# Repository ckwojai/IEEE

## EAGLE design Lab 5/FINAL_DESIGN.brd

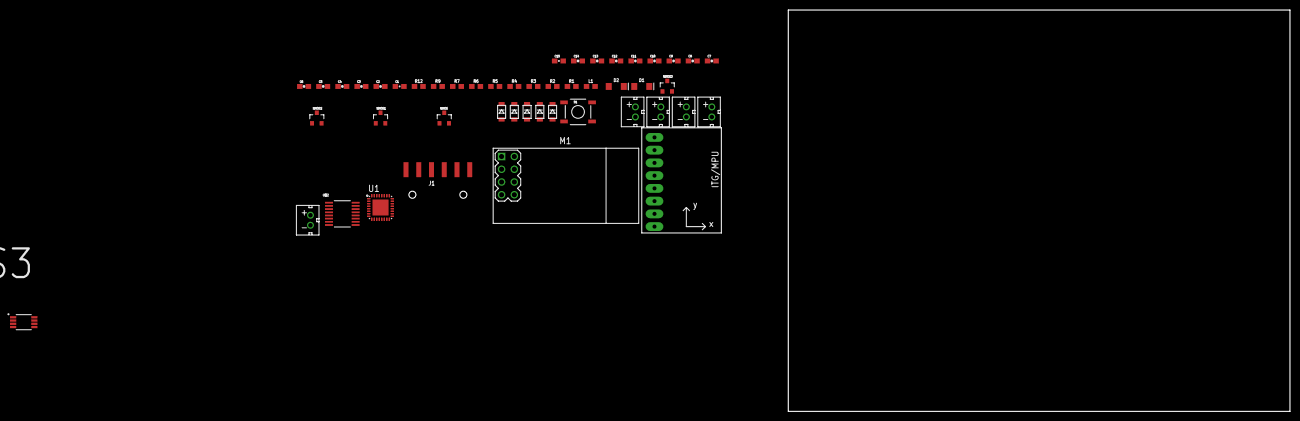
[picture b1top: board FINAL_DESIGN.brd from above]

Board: 2 copper layers, 100.0 x 80.0 mm, 48 parts (0 on the bottom side), 33 nets, no tracks yet.

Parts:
C1, C3, C4, C5, C7, C15: 100nF; 0603-CAP
C2: 10uF; 0603-CAP
C6, C8, C9, C10, C11, C12: 100uF; 0603-CAP
C13: 0.1uF; 0603-CAP
C14: 4.7uF; 0603-CAP
D1, D2: Yellow; LED-1206
DIODE, DIODE1, DIODE2, DIODE3, DIODE4: DB2W40300L; MINI2-F3-B
J1: FTDI_DEVICERA_SMT; FTDI_DEVICE_RA_SMT
L1: 10uH; 0603
M1: WIRELESS-NRF24L01
MOTOR, MOTOR1, MOTOR2, MOTOR3: JST_CONNECTOR_FEMALE
NMOS, NMOS1, NMOS2, NMOS3: N-CHANNEL-MOSFET-IRLML6244TRPBF; SOT23-3
R1, R2: 2.2k; 0603
R3, R4, R5, R6, R7: 10k; 0603
R9, R12: 1k; 0603
S1: SWITCH-MOMENTARY-2SMD; TACTILE-SWITCH-SMD
U1: 3.3V; MLF32-PAD
U2: GY-521MPU6050; GY-521
U$1: JST_CONNECTOR_FEMALE
U$2: MAX1672'MAX1672'; 21-0055H_16
U$3: LTC6930CMS8-8.19LTC6930CMS8-8.19; SOP65P490X110-8N

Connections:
BATTERY+: C6.2, C8.2, C9.2, C10.2, C11.1, DIODE.NEG, DIODE1.NEG, DIODE2.NEG, DIODE3.NEG, L1.1, MOTOR.+, MOTOR1.+, MOTOR2.+, MOTOR3.+, R1.1, U$1.+, U$2.12
FTDI-RX: J1.3, U1.30
FTDI-TX: J1.2, U1.31
GND: C2.2, C3.2, C4.2, C5.2, C6.1, C7.2, C8.1, C9.1, C10.1, C11.2, C12.2, C13.2, C14.2, C15.2, J1.6, M1.1, NMOS.2, NMOS1.2, NMOS2.2, NMOS3.2, R2.1, R4.1, R5.1, R6.1, R7.1, S1.3, U1.3, U1.5, U1.21, U1.PAD, U2.GND, U$1.-, U$2.2, U$2.6, U$2.7, U$2.10, U$2.14, U$3.2, U$3.3, U$3.4, U$3.5, U$3.6
IMU-INT: U1.1, U2.INT
IMU-SCL: D2.C, U2.SCL
IMU-SDA: D1.C, U2.SDA
MEASURE_PIN: R1.2, R2.2, U1.2
MOTOR1: NMOS.1, R4.2, U1.32
MOTOR2: NMOS1.1, R5.2, U1.9
MOTOR3: NMOS2.1, R6.2, U1.10
MOTOR4: NMOS3.1, R7.2, U1.13
unnamed: DIODE4.POS, L1.2, U$2.1
unnamed: C4.1, U1.20
unnamed: R9.2, U1.27
unnamed: DIODE1.POS, MOTOR1.-, NMOS1.3
unnamed: DIODE2.POS, MOTOR2.-, NMOS2.3
unnamed: DIODE.POS, MOTOR.-, NMOS.3
unnamed: DIODE3.POS, MOTOR3.-, NMOS3.3
unnamed: D1.A, R9.1
unnamed: D2.A, R12.1
unnamed: R12.2, U1.28
unnamed: C1.1, J1.1
OSC1: U1.7, U$3.7
RESET: C1.2, R3.1, S1.1, U1.29
RF-CE: M1.3, U1.12
RF-CSN: M1.4, U1.14
RF-MISO: M1.7, U1.16
RF-MOSI: M1.6, U1.15
RF-SCK: M1.5, U1.17
VCC: C2.1, C3.1, C5.1, C7.1, C14.1, C15.1, J1.4, M1.2, R3.2, U1.4, U1.18, U2.VCC, U$2.9, U$3.1, U$3.8
VR-PS: C12.1, DIODE4.NEG, U$2.5, U$2.11
VR-REF: C13.1, U$2.13

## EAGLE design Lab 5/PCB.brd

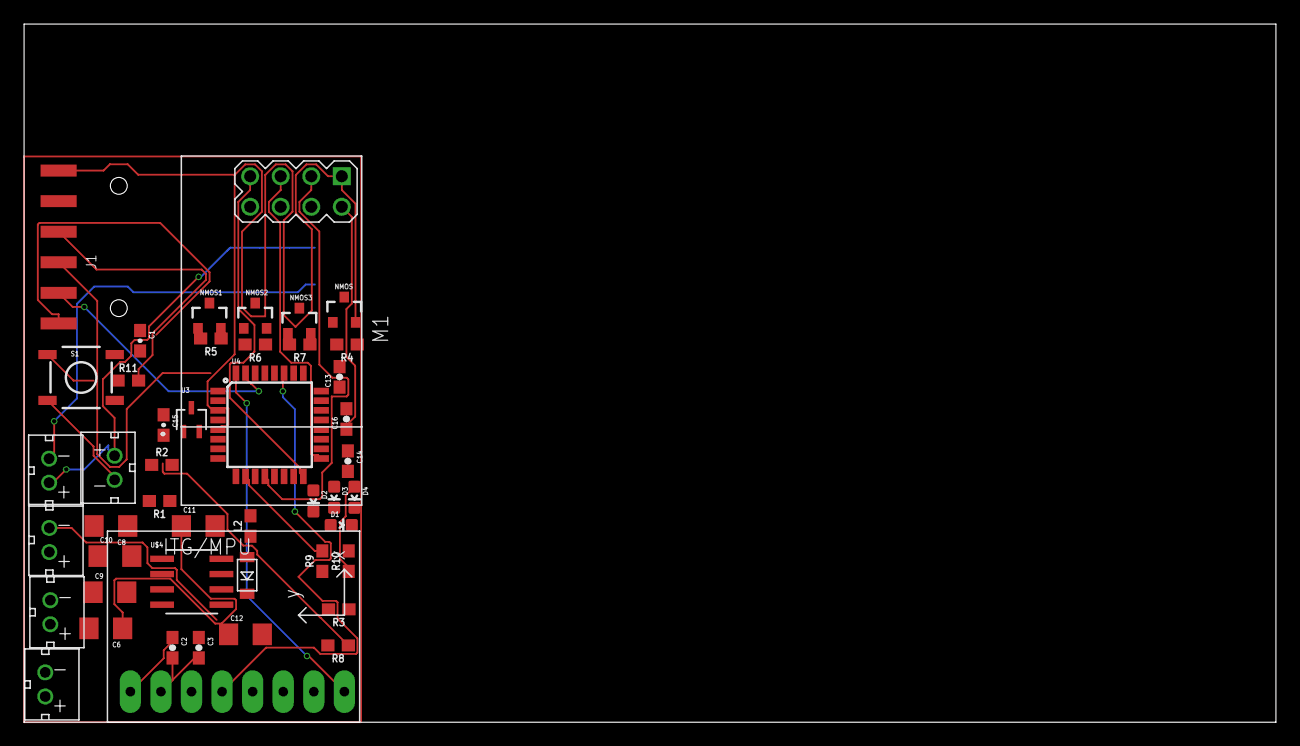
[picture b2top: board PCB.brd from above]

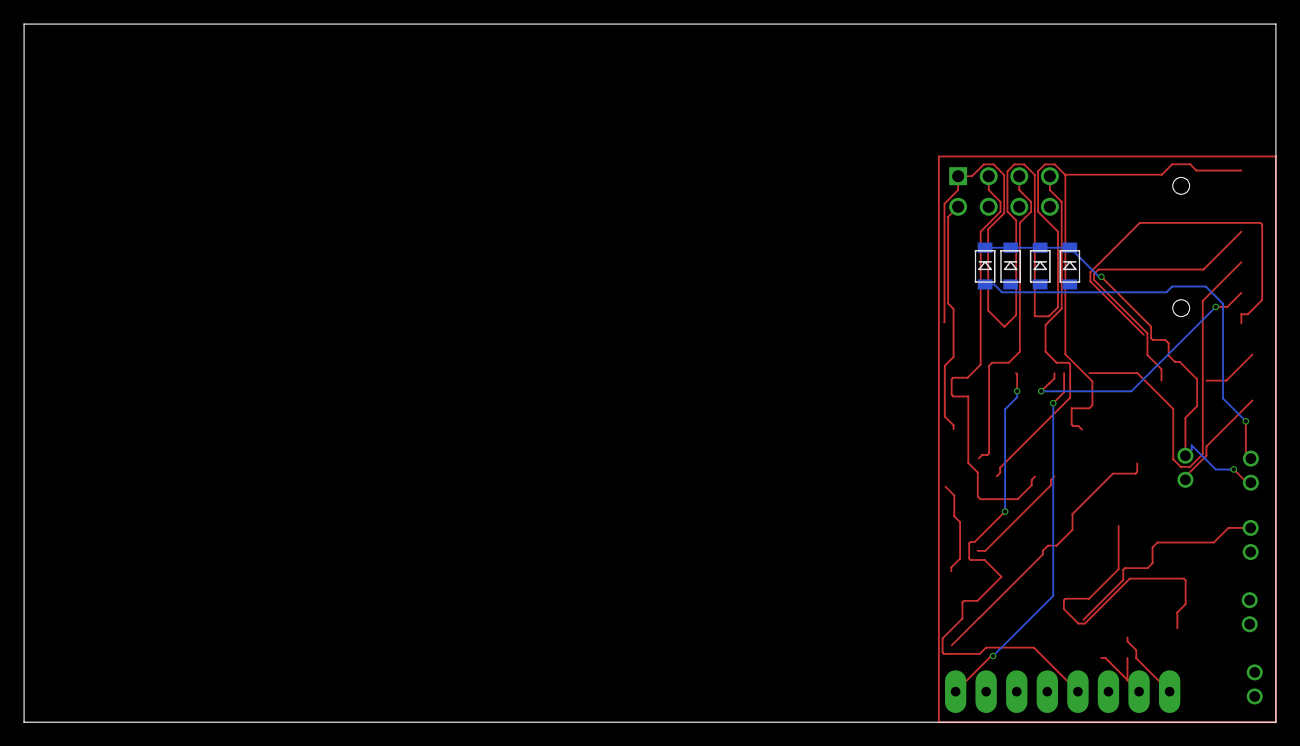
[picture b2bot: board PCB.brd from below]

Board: 4 copper layers, 104.0 x 58.0 mm, 50 parts (4 on the bottom side), 31 nets.

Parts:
BAT: JST_CONNECTOR_FEMALE
C1, C3, C13, C14, C15, C16: 100nF; 0603-CAP
C2: 10uF; 0603-CAP
C6, C8, C9, C10, C11, C12: 100uF; 1206
D1, D2, D3, D4: BLUE; LED-0603
DIODE, DIODE1, DIODE2, DIODE3, DIODE4: DB2W40300L; MINI2-F3-B
J1: FTDI_DEVICERA_SMT; FTDI_DEVICE_RA_SMT
L2: 10uH; 0603
M1: WIRELESS-NRF24L01
MOTOR, MOTOR1, MOTOR2, MOTOR3: JST_CONNECTOR_FEMALE
NMOS, NMOS1, NMOS2, NMOS3: N-CHANNEL-MOSFET-IRLML6244TRPBF; SOT23-3
R1, R2, R3, R8, R9, R10: 2.2k; 0603
R4, R5, R6, R7, R11: 10k; 0603
S1: SWITCH-MOMENTARY-2SMD; TACTILE-SWITCH-SMD
U2: GY-521MPU6050; GY-521
U3: MAX7375AXR805-T; 21-0075D
U4: ATMEGA328P_TQFP; TQFP32-08
U$4: LT1300CS8#PBF-NDLT1300CS8#PBF-ND; SOIC-8_S

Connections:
BATTERY+: BAT.+, C6.2, C8.2, C9.2, C10.2, C11.2, DIODE.NEG, DIODE1.NEG, DIODE2.NEG, DIODE3.NEG, L2.1, MOTOR.+, MOTOR1.+, MOTOR2.+, MOTOR3.+, R1.1, U$4.6
FTDI-RX: J1.3, U4.30
FTDI-TX: J1.2, U4.31
GND: BAT.-, C2.2, C3.2, C6.1, C8.1, C9.1, C10.1, C11.1, C12.1, C13.2, C14.2, C15.2, C16.2, D1.C, D2.C, D3.C, D4.C, J1.6, M1.1, NMOS.2, NMOS1.2, NMOS2.2, NMOS3.2, R2.1, R4.1, R5.1, R6.1, R7.1, S1.3, U2.GND, U3.3, U4.3, U4.5, U4.21, U$4.1, U$4.2, U$4.3, U$4.8
IMU-INT: U2.INT, U4.32
IMU-SCL: U2.SCL, U4.28
IMU-SDA: U2.SDA, U4.27
MEASURE_PIN: R1.2, R2.2, U4.26
MOTOR1: NMOS.1, R3.2, R4.2, U4.1
MOTOR2: NMOS1.1, R5.2, R8.2, U4.9
MOTOR3: NMOS2.1, R6.2, R9.2, U4.10
MOTOR4: NMOS3.1, R7.2, R10.2, U4.13
unnamed: D4.A, R10.1
unnamed: D3.A, R9.1
unnamed: DIODE1.POS, MOTOR1.-, NMOS1.3
unnamed: DIODE2.POS, MOTOR2.-, NMOS2.3
unnamed: DIODE.POS, MOTOR.-, NMOS.3
unnamed: DIODE3.POS, MOTOR3.-, NMOS3.3
unnamed: D2.A, R8.1
unnamed: D1.A, R3.1
unnamed: C1.1, J1.1
unnamed: C13.1, U4.20
OSC1: U3.2, U4.7
RESET: C1.2, R11.1, S1.1, U4.29
RF-CE: M1.3, U4.12
RF-CSN: M1.4, U4.14
RF-MISO: M1.7, U4.16
RF-MOSI: M1.6, U4.15
RF-SCK: M1.5, U4.17
VCC: C2.1, C3.1, C12.2, C14.1, C15.1, C16.1, DIODE4.NEG, J1.4, M1.2, R11.2, U2.VCC, U3.1, U4.4, U4.6, U4.18, U$4.4
VR_SW: DIODE4.POS, L2.2, U$4.7

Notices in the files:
parts and their libraries:
SparkFun-Capacitors: Licensing: Creative Commons ShareAlike 4.0 International - https://creativecommons.org/licenses/by-sa/4.0
